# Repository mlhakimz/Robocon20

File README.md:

# Robocon20
2 Co-op robots playing Rugby 7s based on Fiji's Robocon 2020 theme.

## Mechanical Design

PASS ROBOT

TRY ROBOT

## Electronics Design

PCB BOARD

PCB SCHEMATIC

ARDUINO MEGA CONNECTIONS

ARDUINO NANO CONNECTIONS

INPUT PORTS

OUTPUT PORTS

VOLTMETER CONNECTION

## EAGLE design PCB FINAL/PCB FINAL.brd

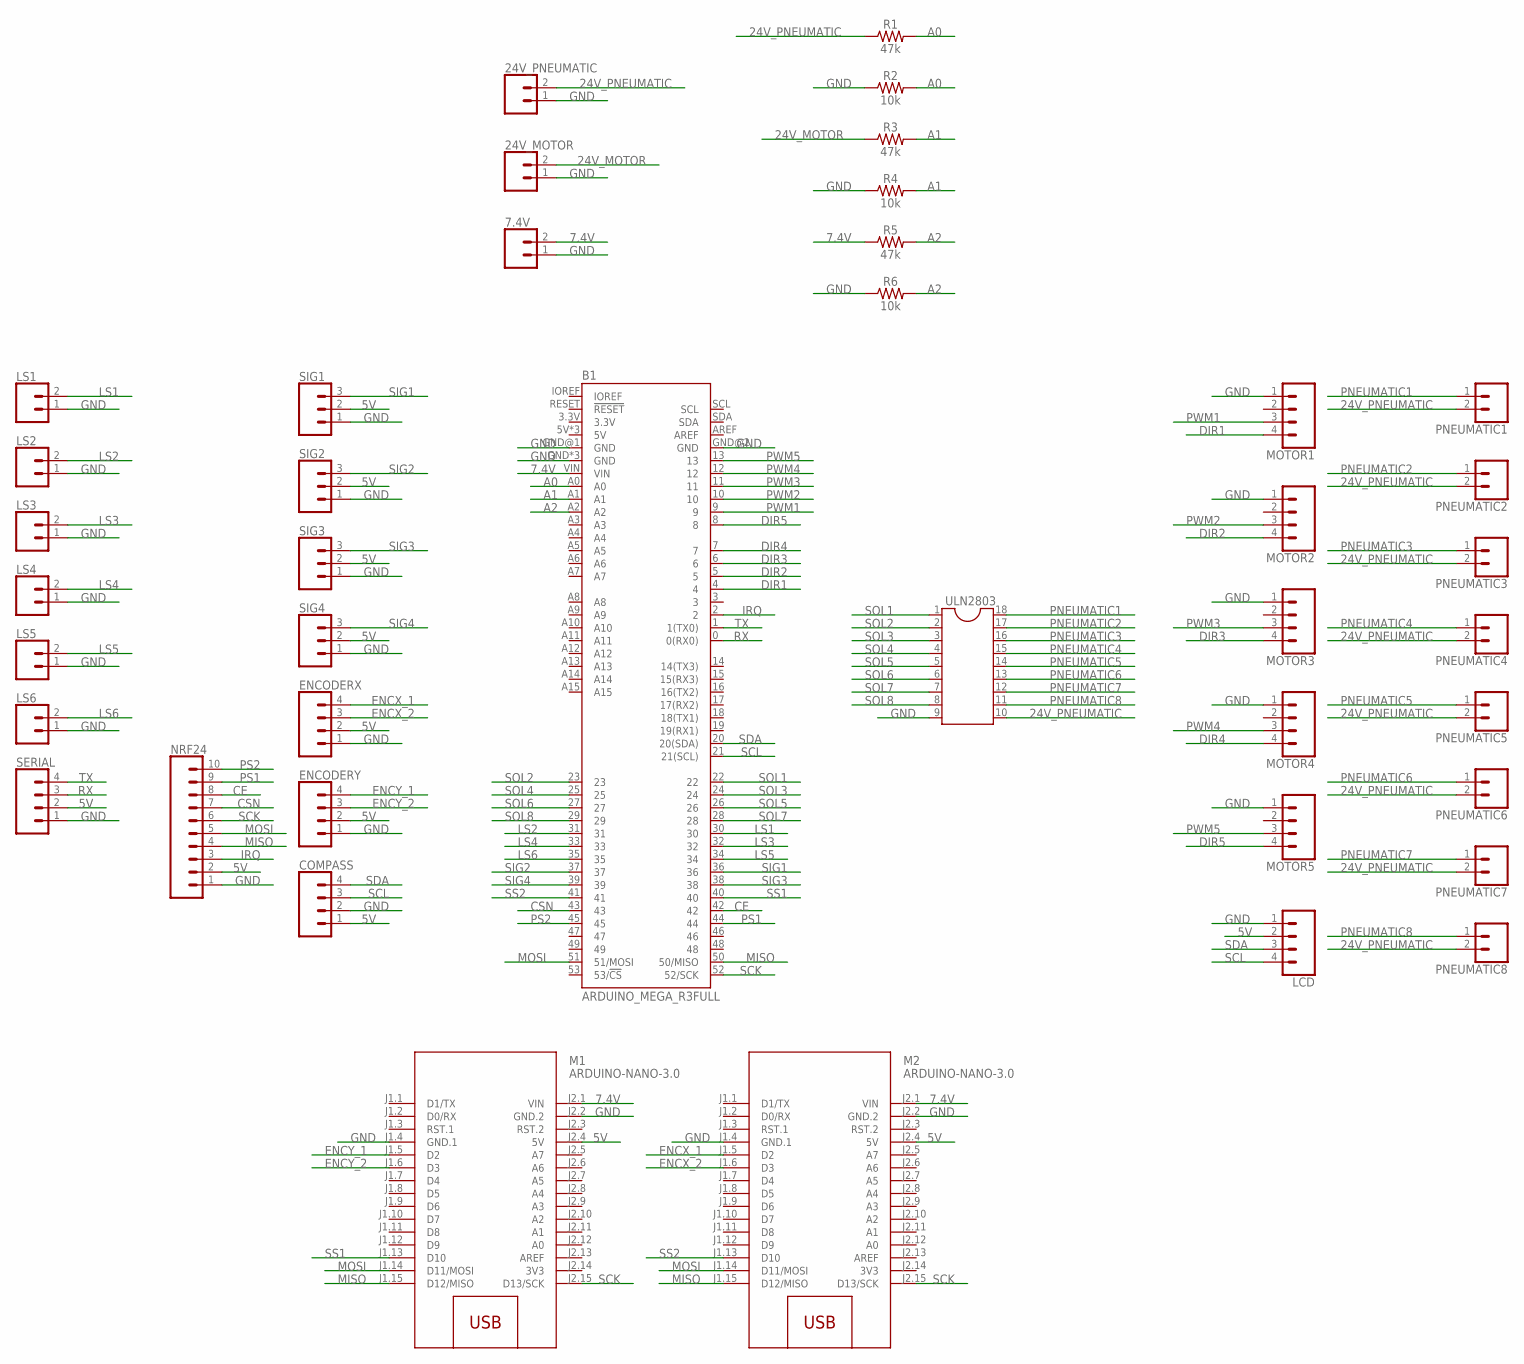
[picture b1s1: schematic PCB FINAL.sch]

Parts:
7.4V, 24V_MOTOR, 24V_PNEUMATIC: CONN_02POLAR_LOCK; MOLEX-1X2_LOCK
B1: ARDUINO_MEGA_R3FULL; ARDUINO_MEGA_NO_SILK
COMPASS: CONN_04POLAR_LOCK; MOLEX-1X4_LOCK
ENCODERX: CONN_04POLAR_LOCK; MOLEX-1X4_LOCK
ENCODERY: CONN_04POLAR_LOCK; MOLEX-1X4_LOCK
LCD: CONN_04POLAR_LOCK; MOLEX-1X4_LOCK
LS1, LS2, LS3, LS4, LS5, LS6: CONN_02POLAR_LOCK; MOLEX-1X2_LOCK
M1, M2: ARDUINO-NANO-3.0
MOTOR1, MOTOR2, MOTOR3, MOTOR4, MOTOR5: CONN_04POLAR_LOCK; MOLEX-1X4_LOCK
NRF24: CONN_10LOCK_LONGPADS; 1X10_LOCK_LONGPADS
PNEUMATIC1, PNEUMATIC2, PNEUMATIC3, PNEUMATIC4, PNEUMATIC5, PNEUMATIC6, PNEUMATIC7, PNEUMATIC8: CONN_02POLAR_LOCK; MOLEX-1X2_LOCK
R1, R3, R5: 47k; AXIAL-0.3
R2, R4, R6: 10k; AXIAL-0.3
SERIAL: CONN_04POLAR_LOCK; MOLEX-1X4_LOCK
SIG1, SIG2, SIG3, SIG4: CONN_03POLAR_LOCK; MOLEX-1X3_LOCK
ULN2803: DIL18S; SOCKET-18

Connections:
3V3: M1.J2.14 (3V3), M2.J2.14 (3V3)
5V: COMPASS.1, ENCODERX.2, ENCODERY.2, LCD.2, M1.J2.4 (5V), M2.J2.4 (5V), NRF24.2, SERIAL.2, SIG1.2, SIG2.2, SIG3.2, SIG4.2
7.4V: 7.4V.2, B1.VIN, M1.J2.1 (VIN), M2.J2.1 (VIN), R5.P$1 (1)
24V_MOTOR: 24V_MOTOR.2, R3.P$1 (1)
24V_PNEUMATIC: 24V_PNEUMATIC.2, PNEUMATIC1.2, PNEUMATIC2.2, PNEUMATIC3.2, PNEUMATIC4.2, PNEUMATIC5.2, PNEUMATIC6.2, PNEUMATIC7.2, PNEUMATIC8.2, R1.P$1 (1), ULN2803.10
A0: B1.A0, R1.P$2 (2), R2.P$2 (2)
A1: B1.A1, R3.P$2 (2), R4.P$2 (2)
A2: B1.A2, R5.P$2 (2), R6.P$2 (2)
CE: B1.42, NRF24.8
CSN: B1.43, NRF24.7
DIR1: B1.4, MOTOR1.4
DIR2: B1.5, MOTOR2.4
DIR3: B1.6, MOTOR3.4
DIR4: B1.7, MOTOR4.4
DIR5: B1.8, MOTOR5.4
ENCX_1: ENCODERX.4, M2.J1.5 (D2)
ENCX_2: ENCODERX.3, M2.J1.6 (D3)
ENCY_1: ENCODERY.4, M1.J1.5 (D2)
ENCY_2: ENCODERY.3, M1.J1.6 (D3)
GND: 7.4V.1, 24V_MOTOR.1, 24V_PNEUMATIC.1, B1.GND, B1.GND@1 (GND), B1.GND@2 (GND), B1.GND@3 (GND), B1.GND@4 (GND), COMPASS.2, ENCODERX.1, ENCODERY.1, LCD.1, LS1.1, LS2.1, LS3.1, LS4.1, LS5.1, LS6.1, M1.J1.4 (GND.1), M1.J2.2 (GND.2), M2.J1.4 (GND.1), M2.J2.2 (GND.2), MOTOR1.1, MOTOR2.1, MOTOR3.1, MOTOR4.1, MOTOR5.1, NRF24.1, R2.P$1 (1), R4.P$1 (1), R6.P$1 (1), SERIAL.1, SIG1.1, SIG2.1, SIG3.1, SIG4.1, ULN2803.9
IRQ: B1.2, NRF24.3
LS1: B1.30, LS1.2
LS2: B1.31, LS2.2
LS3: B1.32, LS3.2
LS4: B1.33, LS4.2
LS5: B1.34, LS5.2
LS6: B1.35, LS6.2
MISO: B1.50 (50/MISO), M1.J1.15 (D12/MISO), M2.J1.15 (D12/MISO), NRF24.4
MOSI: B1.51 (51/MOSI), M1.J1.14 (D11/MOSI), M2.J1.14 (D11/MOSI), NRF24.5
PNEUMATIC1: PNEUMATIC1.1, ULN2803.18
PNEUMATIC2: PNEUMATIC2.1, ULN2803.17
PNEUMATIC3: PNEUMATIC3.1, ULN2803.16
PNEUMATIC4: PNEUMATIC4.1, ULN2803.15
PNEUMATIC5: PNEUMATIC5.1, ULN2803.14
PNEUMATIC6: PNEUMATIC6.1, ULN2803.13
PNEUMATIC7: PNEUMATIC7.1, ULN2803.12
PNEUMATIC8: PNEUMATIC8.1, ULN2803.11
PS1: B1.44, NRF24.9
PS2: B1.45, NRF24.10
PWM1: B1.9, MOTOR1.3
PWM2: B1.10, MOTOR2.3
PWM3: B1.11, MOTOR3.3
PWM4: B1.12, MOTOR4.3
PWM5: B1.13, MOTOR5.3
RX: B1.0 (0(RX0)), SERIAL.3
SCK: B1.52 (52/SCK), M1.J2.15 (D13/SCK), M2.J2.15 (D13/SCK), NRF24.6
SCL: B1.21 (21(SCL)), COMPASS.3, LCD.4
SDA: B1.20 (20(SDA)), COMPASS.4, LCD.3
SIG1: B1.36, SIG1.3
SIG2: B1.37, SIG2.3
SIG3: B1.38, SIG3.3
SIG4: B1.39, SIG4.3
SOL1: B1.22, ULN2803.1
SOL2: B1.23, ULN2803.2
SOL3: B1.24, ULN2803.3
SOL4: B1.25, ULN2803.4
SOL5: B1.26, ULN2803.5
SOL6: B1.27, ULN2803.6
SOL7: B1.28, ULN2803.7
SOL8: B1.29, ULN2803.8
SS1: B1.40, M1.J1.13 (D10)
SS2: B1.41, M2.J1.13 (D10)
TX: B1.1 (1(TX0)), SERIAL.4

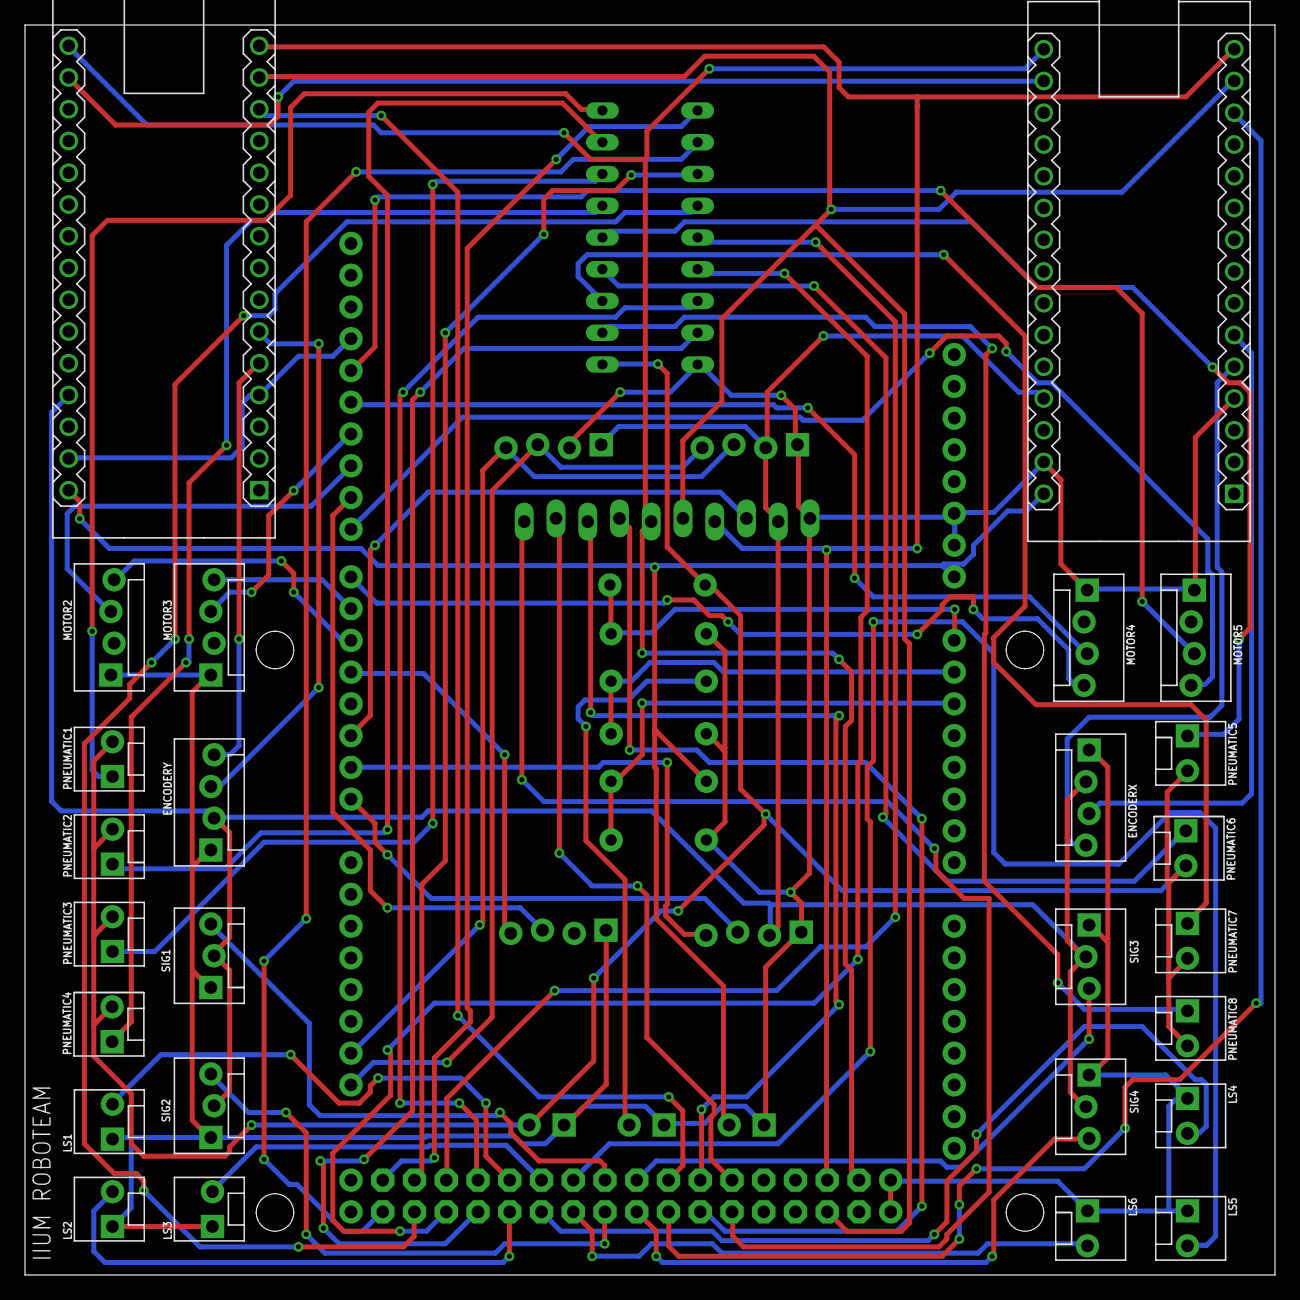
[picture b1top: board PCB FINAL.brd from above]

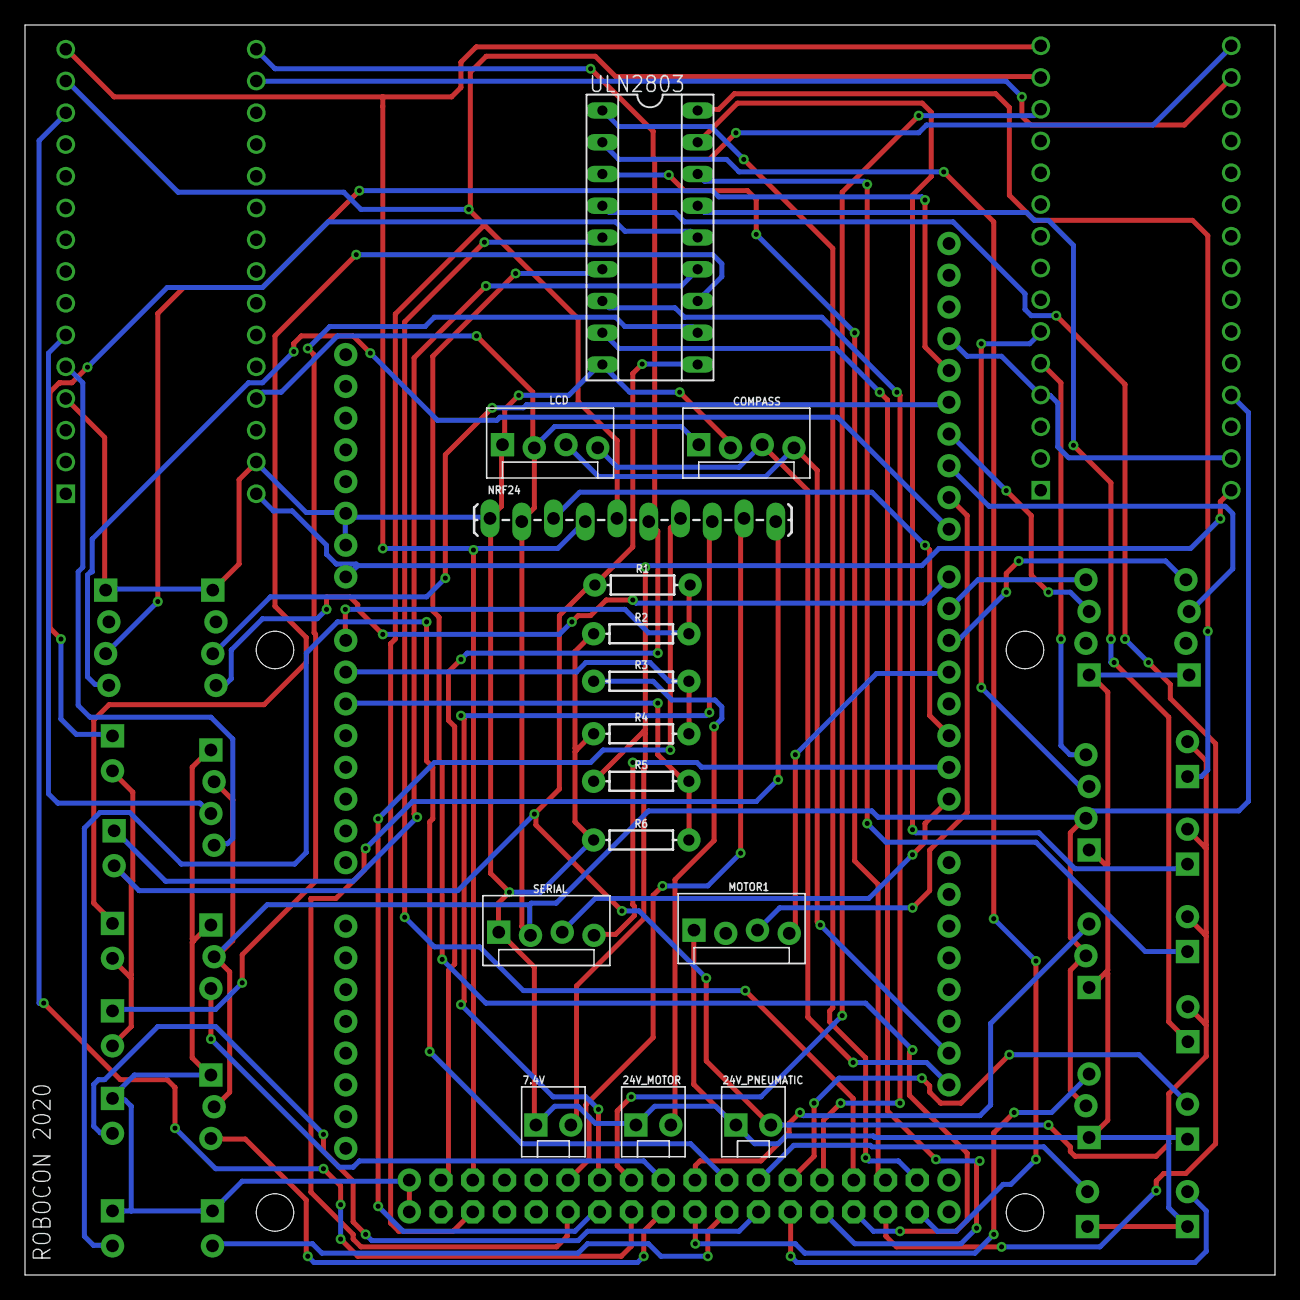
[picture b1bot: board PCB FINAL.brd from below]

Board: 2 copper layers, 100.0 x 100.0 mm, 42 parts (16 on the bottom side), 63 nets.

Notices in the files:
parts and their libraries:
SparkFun-Boards: Licensing: Creative Commons ShareAlike 4.0 International - https://creativecommons.org/licenses/by-sa/4.0
diy-modules: Released under the Creative Commons Attribution 4.0 International License: http://creativecommons.org/licenses/by/4.0
